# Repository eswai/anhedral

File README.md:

# 自作キーボード　ANHEDRAL rev. 1

## 特徴
- 一体型、非分割キーボード
- 完全左右対称、row staggeredなSemiErgoキーレイアウト https://github.com/mtei/SemiErgo_Layout
- 親指シフト対応
  - 親指で押すキーが多いので、専用の親指シフトキーを配置可能
  - QMKでの親指シフト入力が可能(補助ソフトのインストールが不要)
  - modifier行を0.25U下げることで同時押しを容易に
  - https://github.com/eswai/qmk_firmware/tree/master/keyboards/crkbd/keymaps/nicola
- Cherry MXまたは互換キースイッチ専用、ホットスワップ対応
- 104キーキャップ対応

## キーマップの例

eucalyn配列、親指のシフトキーを親指シフトのための親指キーとして使う。
```
//+-------+-------+-------+-------+-------+-------+-------+       +-------+-------+-------+-------+-------+-------+-------+
    KC_TAB,   KC_Q,   KC_W,KC_COMM, KC_DOT,KC_SCLN,KC_MINS,         KC_EQL,   KC_M,   KC_R,   KC_D,   KC_Y,   KC_P,KC_BSLS, \
//+-------+-------+-------+-------+-------+-------+-------+       +-------+-------+-------+-------+-------+-------+-------+
   KC_LCTL,   KC_A,   KC_O,   KC_E,   KC_I,   KC_U,KC_LBRC,        KC_RBRC,   KC_G,   KC_T,   KC_K,   KC_S,   KC_N,KC_RCMD, \
//+-------+-------+-------+-------+-------+-------+-------+-------+-------+-------+-------+-------+-------+-------+-------+
   SFT_ESC,   KC_Z,   KC_X,   KC_C,   KC_V,   KC_F, KC_GRV,KC_BSPC,KC_QUOT,   KC_B,   KC_H,   KC_J,   KC_L,KC_SLSH,KC_RALT, \
//+-------+-------+-------+-------+-------+-------+-------+-------+-------+-------+-------+-------+-------+-------+-------+
                              EISU,  LOWER, KC_SPC,KC_LSFT, KC_DEL,KC_RSFT, KC_ENT,  RAISE,   KANA \
//                        +-------+-------+-------+-------+-------+-------+-------+-------+-------+
```

## BOM 部品リスト
- トッププレート(PCB 1.6mm) 1個
- ボトムプレート(PCB 1.6mm) 1個
- ミドルプレート(PCB 1.6mm) 1個
- ねじ M2 x 4mm 22個
- スペーサ M2 x 7mm 11個
- Pro Micro 1個
- キースイッチ 52個
- ANSI104 キーキャップ 
- 2Uスタビライザー (PCBマウント) 1個
- 表面実装用タクトスイッチ TSHA-T-2.5B2-19E 1個
- ダイオード1N4148(スルーホールまたは表面実装) 52個
- PCBソケット　52個
- ゴム足大 3,4個 
- ゴム足小 3,4個

## ファームウェア
- 公開予定

## 既知の不具合
- ボトムプレートに固定用の穴が一つ足りない
- リセット用のタクトスイッチがトッププレートと干渉するため予定していたスルーホールのスイッチではなく、高さの低い表面実装のタクトスイッチへ変更
- トッププレートが小さく、modifier行の左右の端の1.5Uのキーが少しはみ出す

## 改善したい点
- Pro Microが下側で露出するのは危険なので、ボトムプレートでカバーしたい
- ノートPCの前に置くとケーブルが邪魔なので、横向きにだす
- 親指で押すキーの配置を見直す

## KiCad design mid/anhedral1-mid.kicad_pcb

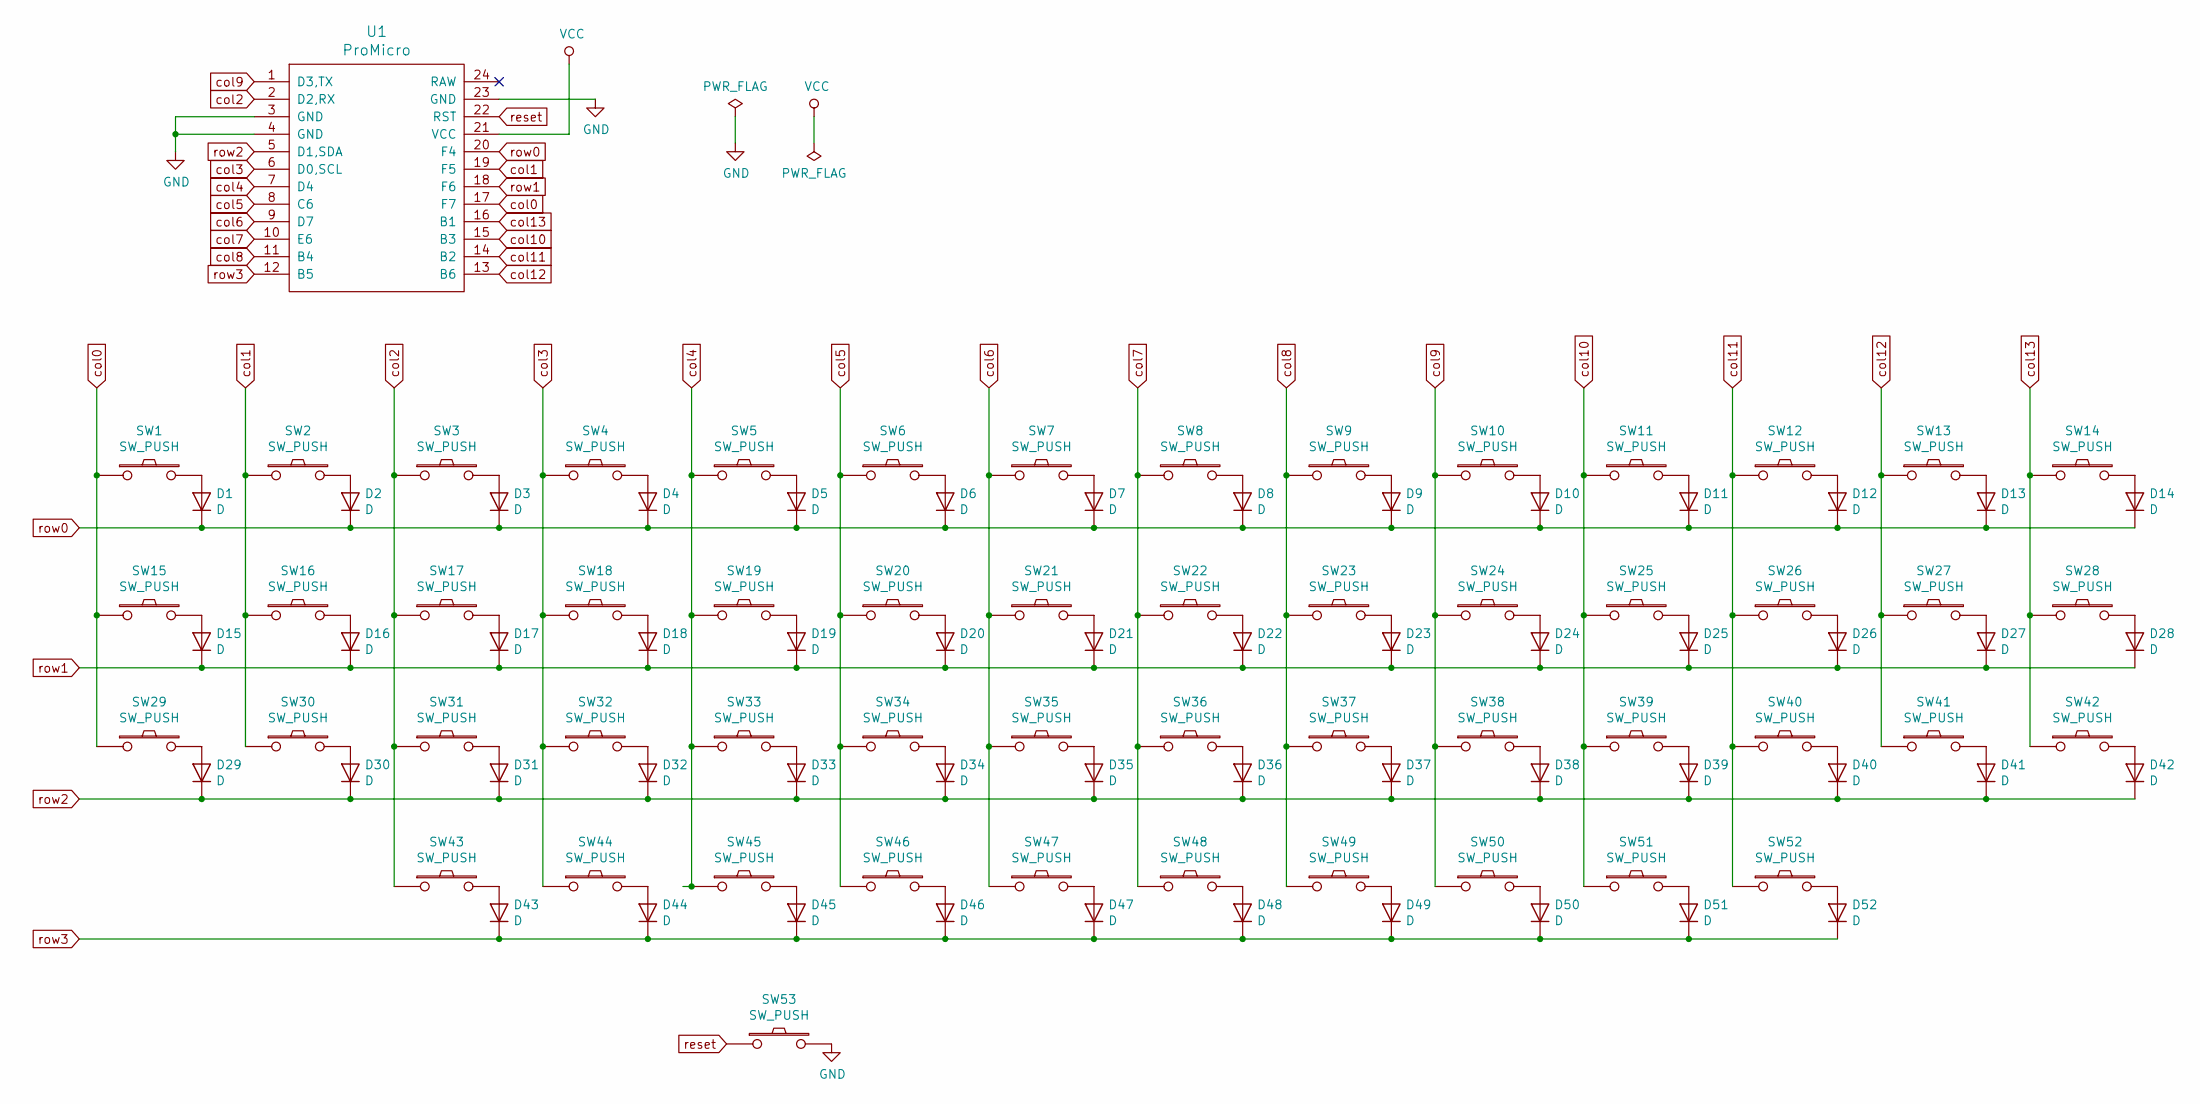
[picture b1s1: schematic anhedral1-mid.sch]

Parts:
D1, D2, D3, D4, D5, D6, D7, D8, D9, D10, D11, D12, D13, D14, D15, D16, D17, D18, D19, D20, D21, D22, D23, D24, D25, D26, D27, D28, D29, D30, D31, D32, D33, D34, D35, D36, D37, D38, D39, D40, D41, D42, D43, D44, D45, D46, D47, D48, D49, D50, D51, D52: D; Diode-dual
SW1, SW2, SW3, SW4, SW5, SW6, SW7, SW8, SW9, SW10, SW11, SW12, SW13, SW14, SW15, SW16, SW17, SW18, SW19, SW20, SW21, SW22, SW23, SW24, SW25, SW26, SW27, SW28, SW29, SW30, SW31, SW32, SW33, SW34, SW35, SW36, SW37, SW38, SW39, SW40, SW41, SW42, SW43, SW44, SW45, SW46, SW48, SW49, SW50, SW51, SW52: SW_PUSH; CherryMX_Hotswap
SW47: SW_PUSH; CherryMX_Hotswap_2u
SW53: SW_PUSH; ResetSW_4P
U1: ProMicro; ArduinoProMicro

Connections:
GND: SW53.2, U1.3 (GND), U1.4 (GND), U1.23 (GND)
unnamed: D1.2 (A), SW1.2
unnamed: D2.2 (A), SW2.2
unnamed: D3.2 (A), SW3.2
unnamed: D4.2 (A), SW4.2
unnamed: D5.2 (A), SW5.2
unnamed: D6.2 (A), SW6.2
unnamed: D7.2 (A), SW7.2
unnamed: D8.2 (A), SW8.2
unnamed: D9.2 (A), SW9.2
unnamed: D10.2 (A), SW10.2
unnamed: D11.2 (A), SW11.2
unnamed: D12.2 (A), SW12.2
unnamed: D13.2 (A), SW13.2
unnamed: D14.2 (A), SW14.2
unnamed: D15.2 (A), SW15.2
unnamed: D16.2 (A), SW16.2
unnamed: D17.2 (A), SW17.2
unnamed: D18.2 (A), SW18.2
unnamed: D19.2 (A), SW19.2
unnamed: D20.2 (A), SW20.2
unnamed: D21.2 (A), SW21.2
unnamed: D22.2 (A), SW22.2
unnamed: D23.2 (A), SW23.2
unnamed: D24.2 (A), SW24.2
unnamed: D25.2 (A), SW25.2
unnamed: D26.2 (A), SW26.2
unnamed: D27.2 (A), SW27.2
unnamed: D28.2 (A), SW28.2
unnamed: D29.2 (A), SW29.2
unnamed: D30.2 (A), SW30.2
unnamed: D31.2 (A), SW31.2
unnamed: D32.2 (A), SW32.2
unnamed: D33.2 (A), SW33.2
unnamed: D34.2 (A), SW34.2
unnamed: D35.2 (A), SW35.2
unnamed: D36.2 (A), SW36.2
unnamed: D37.2 (A), SW37.2
unnamed: D38.2 (A), SW38.2
unnamed: D39.2 (A), SW39.2
unnamed: D40.2 (A), SW40.2
unnamed: D41.2 (A), SW41.2
unnamed: D42.2 (A), SW42.2
unnamed: D43.2 (A), SW43.2
unnamed: D44.2 (A), SW44.2
unnamed: D45.2 (A), SW45.2
unnamed: D46.2 (A), SW46.2
unnamed: D47.2 (A), SW47.2
unnamed: D48.2 (A), SW48.2
unnamed: D49.2 (A), SW49.2
unnamed: D50.2 (A), SW50.2
unnamed: D51.2 (A), SW51.2
unnamed: D52.2 (A), SW52.2
VCC: U1.21 (VCC)
col0: SW1.1, SW15.1, SW29.1, U1.17 (F7)
col1: SW2.1, SW16.1, SW30.1, U1.19 (F5)
col2: SW3.1, SW17.1, SW31.1, SW43.1, U1.2 (D2,RX)
col3: SW4.1, SW18.1, SW32.1, SW44.1, U1.6 (D0,SCL)
col4: SW5.1, SW19.1, SW33.1, SW45.1, U1.7 (D4)
col5: SW6.1, SW20.1, SW34.1, SW46.1, U1.8 (C6)
col6: SW7.1, SW21.1, SW35.1, SW47.1, U1.9 (D7)
col7: SW8.1, SW22.1, SW36.1, SW48.1, U1.10 (E6)
col8: SW9.1, SW23.1, SW37.1, SW49.1, U1.11 (B4)
col9: SW10.1, SW24.1, SW38.1, SW50.1, U1.1 (D3,TX)
col10: SW11.1, SW25.1, SW39.1, SW51.1, U1.15 (B3)
col11: SW12.1, SW26.1, SW40.1, SW52.1, U1.14 (B2)
col12: SW13.1, SW27.1, SW41.1, U1.13 (B6)
col13: SW14.1, SW28.1, SW42.1, U1.16 (B1)
reset: SW53.1, U1.22 (RST)
row0: D1.1 (K), D2.1 (K), D3.1 (K), D4.1 (K), D5.1 (K), D6.1 (K), D7.1 (K), D8.1 (K), D9.1 (K), D10.1 (K), D11.1 (K), D12.1 (K), D13.1 (K), D14.1 (K), U1.20 (F4)
row1: D15.1 (K), D16.1 (K), D17.1 (K), D18.1 (K), D19.1 (K), D20.1 (K), D21.1 (K), D22.1 (K), D23.1 (K), D24.1 (K), D25.1 (K), D26.1 (K), D27.1 (K), D28.1 (K), U1.18 (F6)
row2: D29.1 (K), D30.1 (K), D31.1 (K), D32.1 (K), D33.1 (K), D34.1 (K), D35.1 (K), D36.1 (K), D37.1 (K), D38.1 (K), D39.1 (K), D40.1 (K), D41.1 (K), D42.1 (K), U1.5 (D1,SDA)
row3: D43.1 (K), D44.1 (K), D45.1 (K), D46.1 (K), D47.1 (K), D48.1 (K), D49.1 (K), D50.1 (K), D51.1 (K), D52.1 (K), U1.12 (B5)

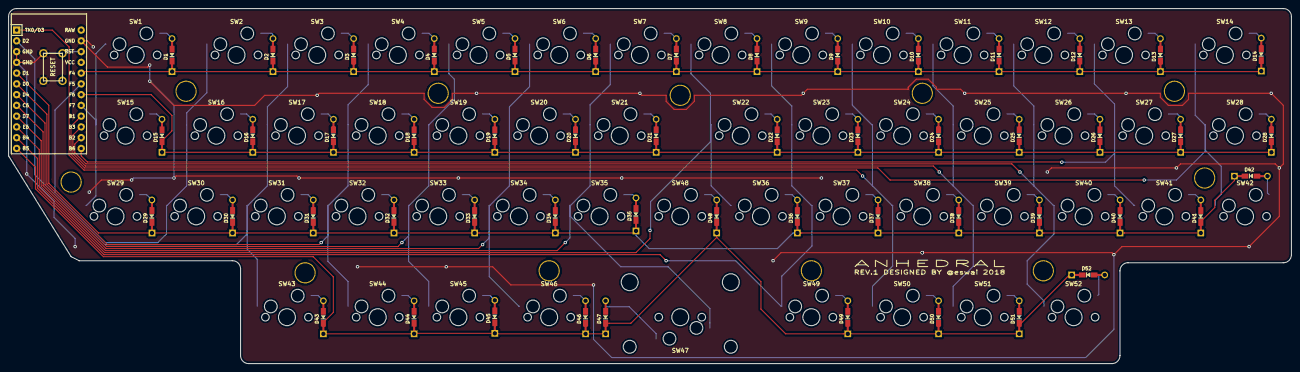
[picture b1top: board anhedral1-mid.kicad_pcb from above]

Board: 2 copper layers, 302.9 x 83.8 mm, 117 parts (0 on the bottom side), 72 nets.

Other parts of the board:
Ref**: Val**; HOLE
Ref**#2, Ref**#3, Ref**#4, Ref**#5, Ref**#6, Ref**#7, Ref**#8, Ref**#9, Ref**#10, Ref**#11: Val**; HOLE

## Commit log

2019-01-05 Initial release
2019-01-05 README
2019-01-05 picture
2019-01-05 picture crop
2019-01-05 keymap
